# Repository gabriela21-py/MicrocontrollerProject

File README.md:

# Electronic Monitoring System Project

## Project Overview
This project is a **medium-complexity electronic monitoring system** based on a microcontroller. It reads data from sensors (temperature and light), displays information on an LCD, controls LEDs and a buzzer, and allows user interaction via buttons.

---

## Defined Design Requirements
- Designed a **medium-complexity electronic board** including:
  - LCD  
  - Temperature sensor  
  - Buzzer  
  - LEDs  
  - Buttons  
  - Voltage regulator  
- Created a **block diagram** representing the main components and their interconnections.  
- Implemented the system at the **discrete component level**.  
- Developed the **layout for the electronic board**.

---

## Block Diagram
    +-------------------+
    |  Voltage Regulator|
    |       LM7805      |
    +---------+---------+
              |
              v
     +--------+--------+
     |  Microcontroller |
     |    PIC16F877A    |
     +---+---+---+---+--+
         |   |   |   |
         v   v   v   v
       LCD  LEDs Buzzer Sensors
                |         |
                |         +------> Temperature Sensor (TMP36)
                |         +------> Light Sensor (LDR)
         Buttons

---

## Block Description

### 1. Voltage Regulator (100)
- Uses **LM7805** to provide stable +5V.  
- Powers microcontroller and other components.

### 2. Microcontroller (200)
- **PIC16F877A** or similar.  
- Connected to LCD, LEDs, buzzer, sensors, and buttons.

### 3. LCD (300)
- 16x2 display.  
- Displays real-time sensor data and system status.

### 4. LEDs (400)
- Four LEDs controlled via **BC817 transistors**.  
- Indicate system states or alerts.

### 5. Buzzer (500)
- Activated via **BC817 transistor**.  
- Provides audible notifications.

### 6. Temperature Sensor (600)
- **TMP36** analog sensor.  
- Sends analog voltage to microcontroller.

### 7. Light Sensor (700)
- **LDR** with voltage divider.  
- Measures ambient light.

### 8. Buttons (800)
- Three push buttons with **pull-down resistors**.  
- Allow user to interact (mode change, reset, etc.).

### 9. Connector (900)
- For programming or external module connection.  
- Provides power and communication pins.

---

## PCB Manufacturing Sponsor

This PCB was kindly sponsored by **PCBWay**, who provided fabrication support for this project.

I would like to thank PCBWay for:
- High PCB manufacturing quality  
- Fast order processing & delivery  
- Professional communication and support  

More about their services:  
➡️https://m.pcbway.com/

## 🖼️ PCB Preview

### 🔹 Top View

### 🔹 Bottom View

## Summary
This project demonstrates the design, implementation, and layout of a medium-complexity electronic board capable of **monitoring environmental parameters**, **displaying data**, and **interacting with users** through LEDs, buzzer, and buttons.

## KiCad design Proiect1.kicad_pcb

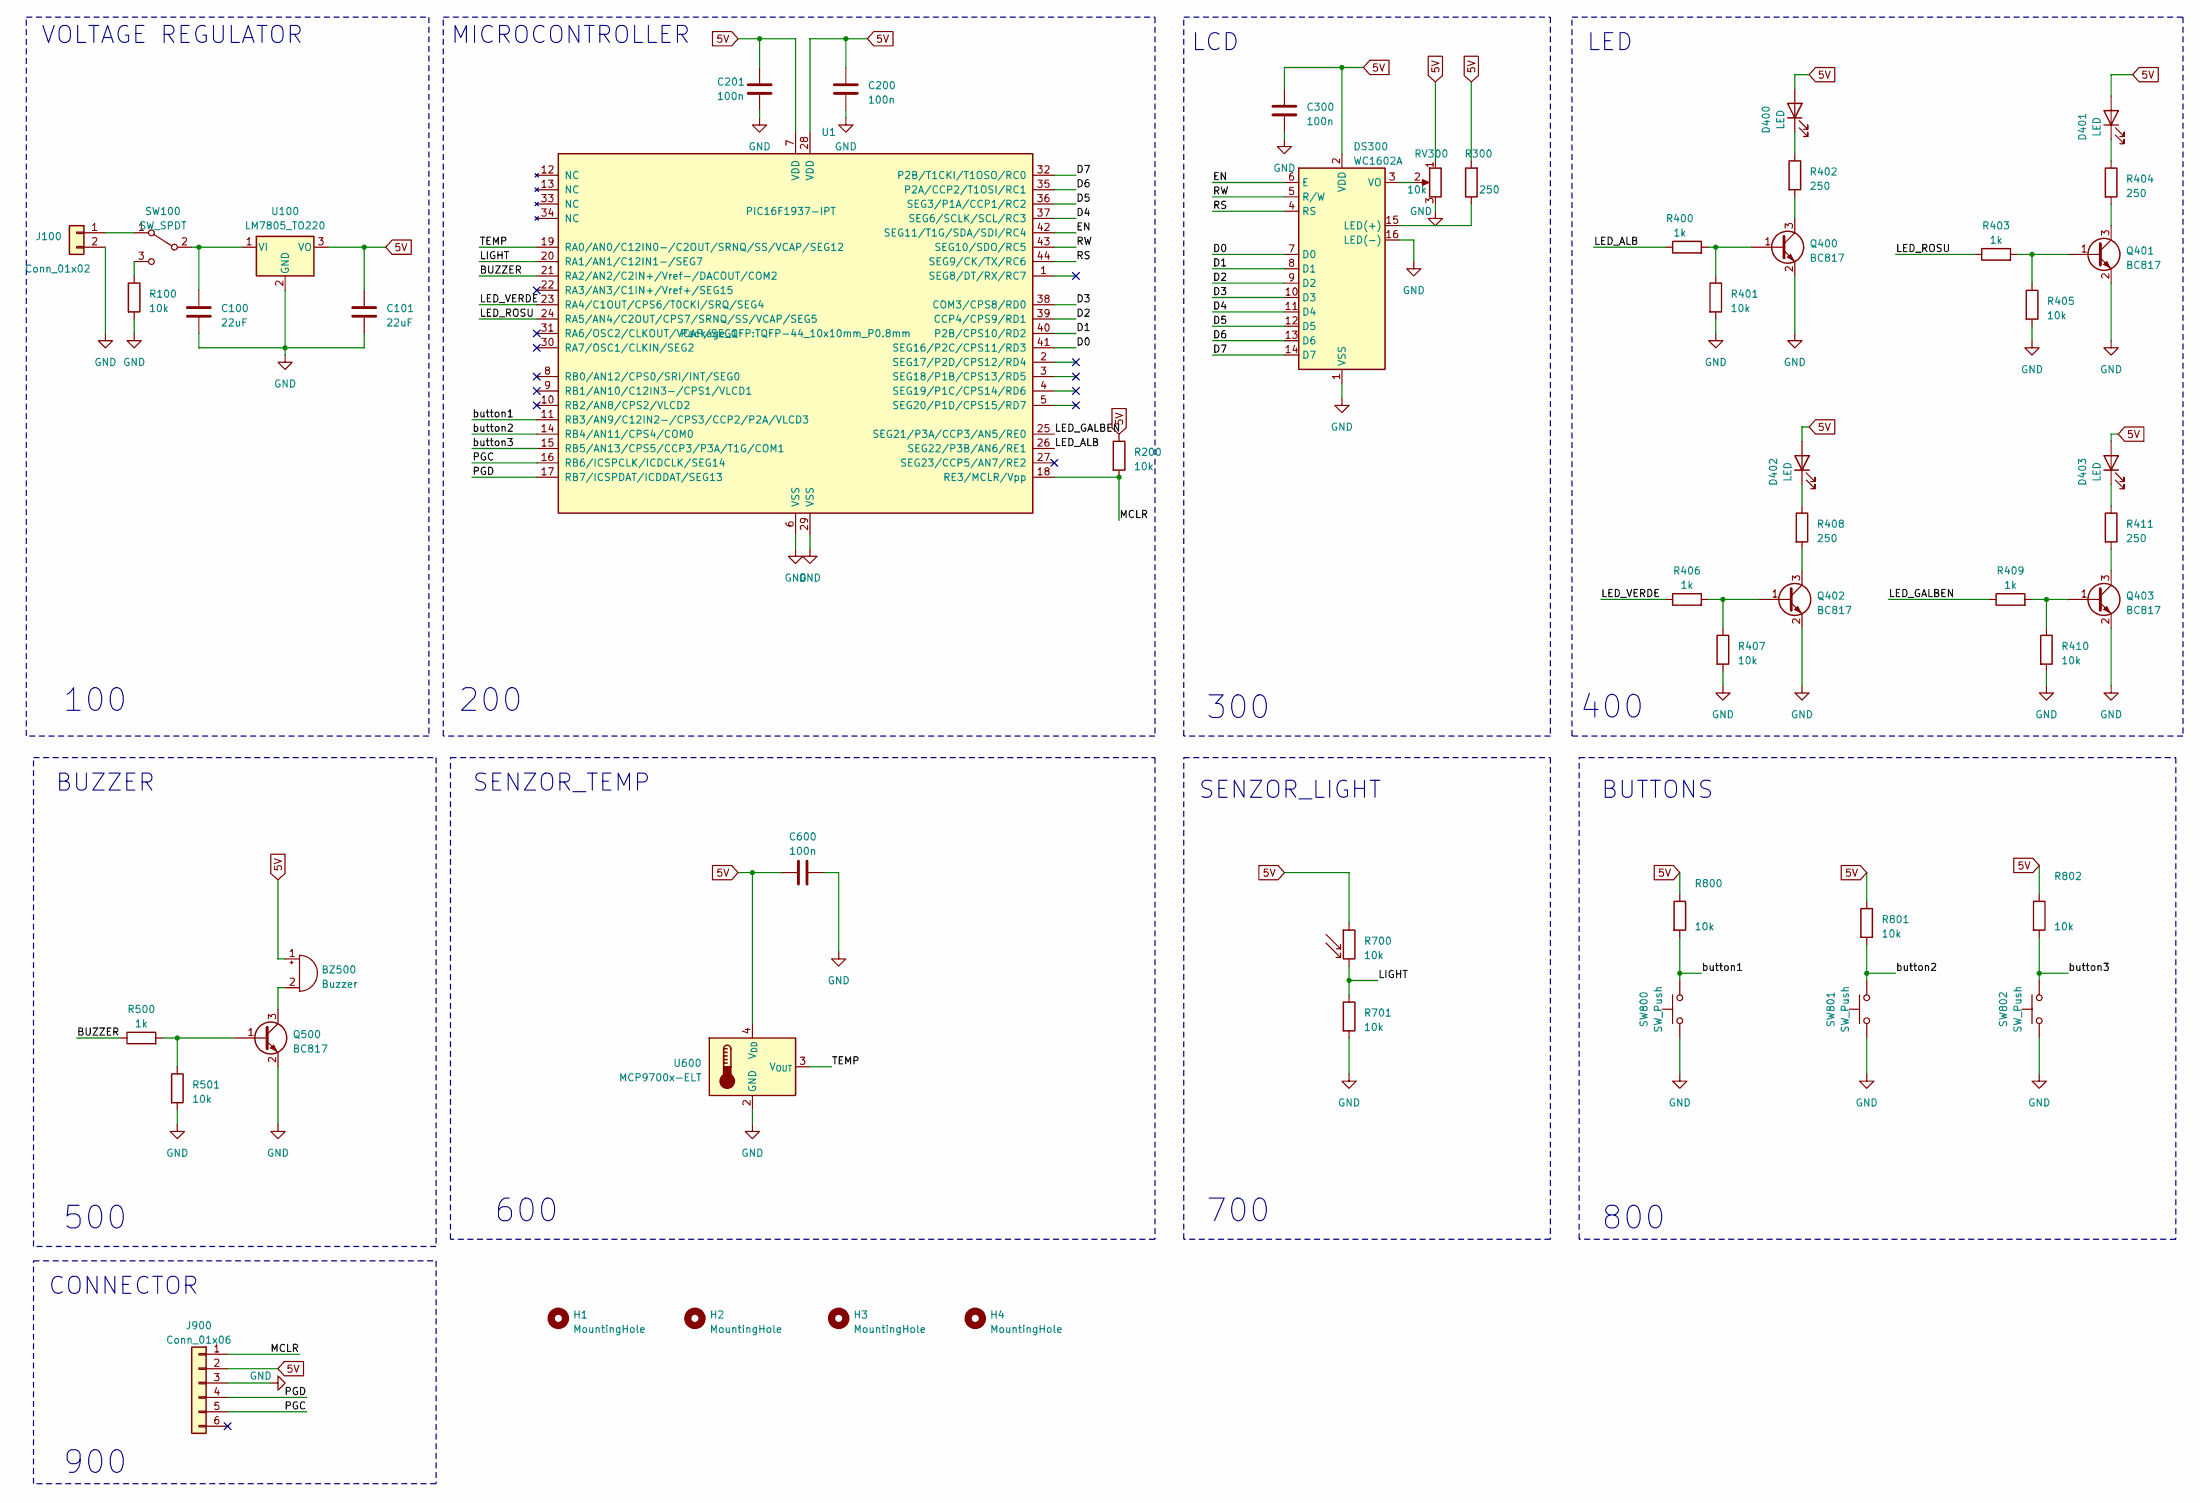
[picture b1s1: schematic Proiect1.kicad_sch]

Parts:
BZ500: Buzzer; Buzzer_12x9.5RM7.6
C100, C101: 22uF; C_1206_3216Metric_Pad1.33x1.80mm_HandSolder
C200, C201, C300, C600: 100n; C_0805_2012Metric_Pad1.18x1.45mm_HandSolder
D400, D401, D402, D403: LED; LED_0805_2012Metric_Pad1.15x1.40mm_HandSolder
DS300: WC1602A
H1, H2, H3, H4: MountingHole; MountingHole_4.3mm_M4_DIN965_Pad
J100: Conn_01x02; TerminalBlock_Phoenix_MKDS-1,5-2_1x02_P5.00mm_Horizontal
J900: Conn_01x06; PinHeader_1x06_P2.54mm_Vertical
Q400, Q401, Q402, Q403, Q500: BC817; SOT-23
R100, R200, R401, R405, R407, R410, R501, R701, R800, R801, R802: 10k; R_0805_2012Metric_Pad1.20x1.40mm_HandSolder
R300, R402, R404, R408, R411: 250; R_0805_2012Metric_Pad1.20x1.40mm_HandSolder
R400, R403, R406, R409, R500: 1k; R_0805_2012Metric_Pad1.20x1.40mm_HandSolder
R700: 10k; R_LDR_D6.4mm_P3.4mm_Vertical
RV300: 10k; Potentiometer_Bourns_3339H_Vertical
SW100: SW_SPDT; PinHeader_1x03_P2.54mm_Vertical
SW800, SW801, SW802: SW_Push; SW_PUSH_6mm_H7.3mm
U1: PIC16F1937-IPT; TQFP-44_10x10mm_P0.8mm
U100: LM7805_TO220; TO-220-3_Vertical
U600: MCP9700x-ELT; SOT-353_SC-70-5

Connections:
5V: BZ500.1 (-), C101.1, C200.1, C201.1, C300.1, C600.2, D400.2 (A), D401.2 (A), D402.2 (A), D403.2 (A), DS300.2 (VDD), J900.2, R200.1, R300.2, R700.1, R800.1, R801.1, R802.1, RV300.1, U1.7 (VDD), U1.28 (VDD), U100.3 (VO), U600.4 (V_{DD})
/BUZZER: R500.1, U1.21 (RA2/AN2/C2IN+/Vref-/DACOUT/COM2)
/D0: DS300.7 (D0), U1.41 (SEG16/P2C/CPS11/RD3)
/D1: DS300.8 (D1), U1.40 (P2B/CPS10/RD2)
/D2: DS300.9 (D2), U1.39 (CCP4/CPS9/RD1)
/D3: DS300.10 (D3), U1.38 (COM3/CPS8/RD0)
/D4: DS300.11 (D4), U1.37 (SEG6/SCLK/SCL/RC3)
/D5: DS300.12 (D5), U1.36 (SEG3/P1A/CCP1/RC2)
/D6: DS300.13 (D6), U1.35 (P2A/CCP2/T1OSI/RC1)
/D7: DS300.14 (D7), U1.32 (P2B/T1CKI/T1OSO/RC0)
/EN: DS300.6 (E), U1.42 (SEG11/T1G/SDA/SDI/RC4)
/LED_ALB: R400.1, U1.26 (SEG22/P3B/AN6/RE1)
/LED_GALBEN: R409.1, U1.25 (SEG21/P3A/CCP3/AN5/RE0)
/LED_ROSU: R403.1, U1.24 (RA5/AN4/C2OUT/CPS7/SRNQ/SS/VCAP/SEG5)
/LED_VERDE: R406.1, U1.23 (RA4/C1OUT/CPS6/T0CKI/SRQ/SEG4)
/LIGHT: R700.2, R701.1, U1.20 (RA1/AN1/C12IN1-/SEG7)
/MCLR: J900.1, R200.2, U1.18 (RE3/MCLR/Vpp)
/PGC: J900.5, U1.16 (RB6/ICSPCLK/ICDCLK/SEG14)
/PGD: J900.4, U1.17 (RB7/ICSPDAT/ICDDAT/SEG13)
/RS: DS300.4 (RS), U1.44 (SEG9/CK/TX/RC6)
/RW: DS300.5 (R/W), U1.43 (SEG10/SDO/RC5)
/TEMP: U1.19 (RA0/AN0/C12IN0-/C2OUT/SRNQ/SS/VCAP/SEG12), U600.3 (V_{OUT})
/button1: R800.2, SW800.2, U1.11 (RB3/AN9/C12IN2-/CPS3/CCP2/P2A/VLCD3)
/button2: R801.2, SW801.2, U1.14 (RB4/AN11/CPS4/COM0)
/button3: R802.2, SW802.2, U1.15 (RB5/AN13/CPS5/CCP3/P3A/T1G/COM1)
GND: C100.2, C101.2, C200.2, C201.2, C300.2, C600.1, DS300.1 (VSS), DS300.16 (LED(-)), J100.2, J900.3, Q400.2 (E), Q401.2 (E), Q402.2 (E), Q403.2 (E), Q500.2 (E), R100.2, R401.2, R405.2, R407.2, R410.2, R501.2, R701.2, RV300.3, SW800.1, SW801.1, SW802.1, U1.6 (VSS), U1.29 (VSS), U100.2 (GND), U600.2 (GND)
unnamed: BZ500.2 (+), Q500.3 (C)
unnamed: D400.1 (K), R402.1
unnamed: D401.1 (K), R404.1
unnamed: D402.1 (K), R408.1
unnamed: D403.1 (K), R411.1
unnamed: DS300.15 (LED(+)), R300.1
unnamed: DS300.3 (VO), RV300.2
unnamed: J100.1, SW100.1 (A)
unnamed: Q400.1 (B), R400.2, R401.1
unnamed: Q400.3 (C), R402.2
unnamed: Q401.1 (B), R403.2, R405.1
unnamed: Q401.3 (C), R404.2
unnamed: Q402.1 (B), R406.2, R407.1
unnamed: Q402.3 (C), R408.2
unnamed: Q403.1 (B), R409.2, R410.1
unnamed: Q403.3 (C), R411.2
unnamed: Q500.1 (B), R500.2, R501.1
unnamed: C100.1, SW100.2 (B), U100.1 (VI)
unnamed: R100.1, SW100.3 (C)

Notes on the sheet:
100
400
VOLTAGE REGULATOR
700
BUZZER
MICROCONTROLLER
SENZOR_TEMP
SENZOR_LIGHT
CONNECTOR
800
200
900
500
600
BUTTONS
LED
LCD
300

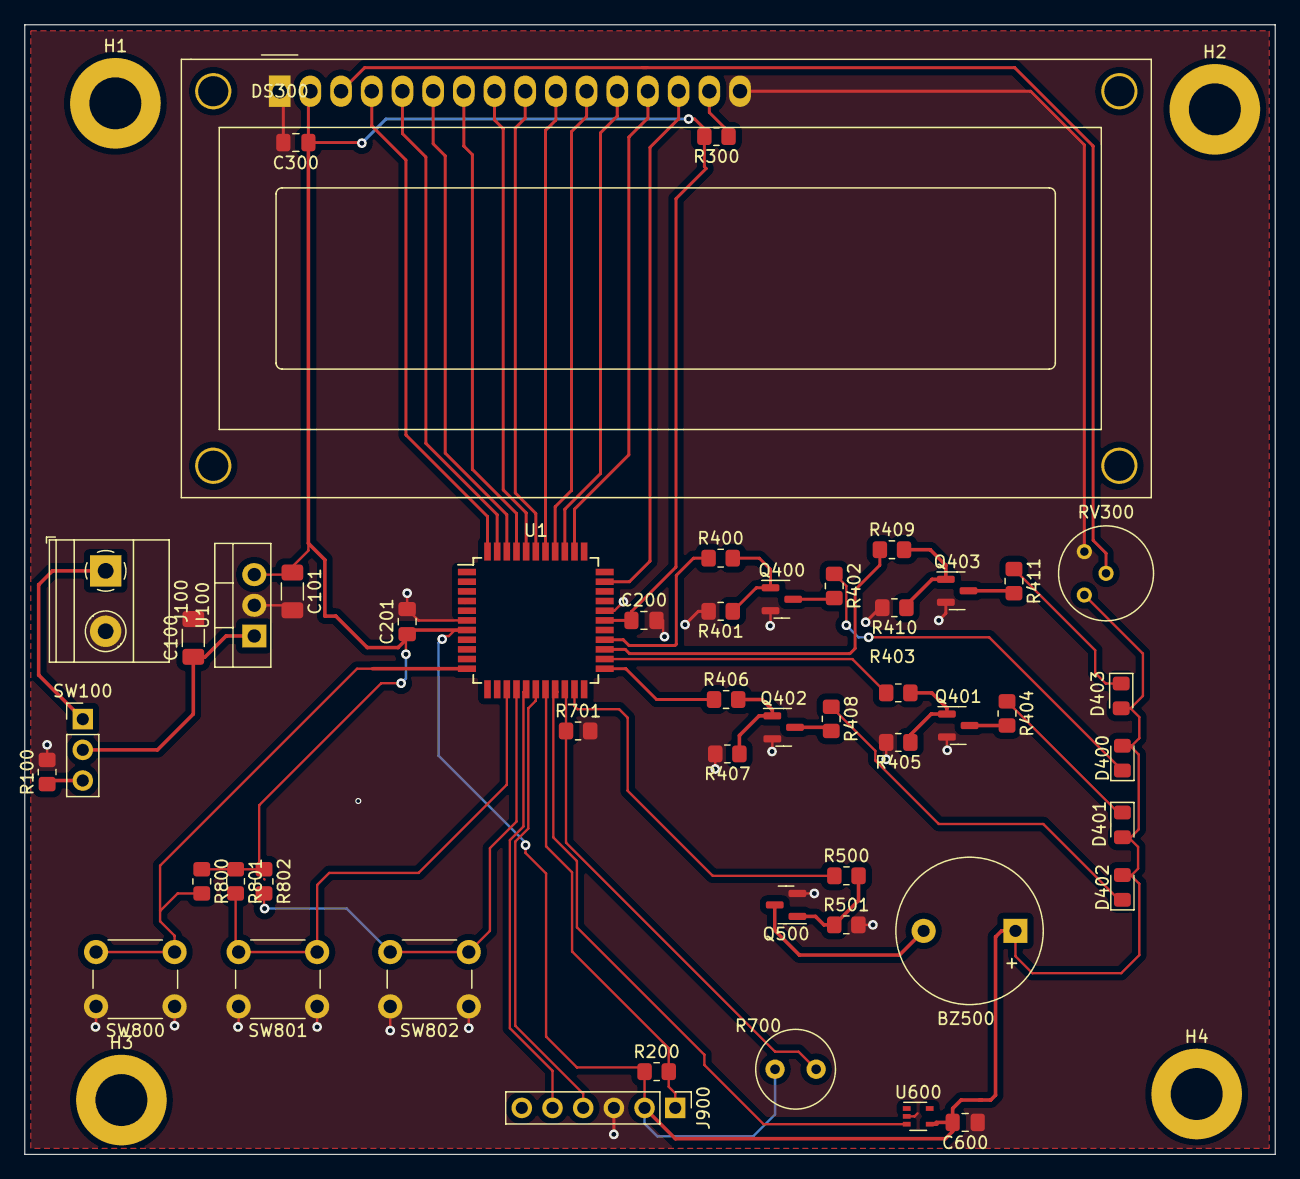
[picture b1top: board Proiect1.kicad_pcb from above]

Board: 2 copper layers, 103.5 x 93.5 mm, 53 parts (0 on the bottom side), 45 nets.

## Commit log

2025-10-14 Initial commit: added project files
2025-10-14 Remove local backup files from repository and ignore folder
2025-10-29 Add PCBWay folder
